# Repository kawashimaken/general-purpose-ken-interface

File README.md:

# KEN Interface

A modular, multi-MCU prototyping platform with a unified pin-assignment standard and horizontally-stackable expansion boards.

> **Status**: Hardware design (KiCad) is published in this repository. Software libraries (Hardware Abstraction Layer and demo applications) are **under active development** and will be released separately in the near future.

---

## 📺 Watch the Introduction

---

## What is KEN Interface?

At its core, **KEN Interface is a standardized pin-assignment pattern shared between MCU boards and expansion boards.**

If you have worked with Arduino shields, the idea will feel familiar — because the pin layout is fixed, any compatible expansion board just plugs straight in and works. KEN Interface follows the same philosophy, but with a few key differences.

### Three Distinctive Features

#### 1. Horizontal Expansion

Instead of stacking boards vertically like Arduino shields, KEN Interface uses **15×2 right-angle pin headers** so boards connect **side by side**. The left and right connectors are completely symmetrical — it does not matter which side you plug into.

Add a **junction board** into the mix, and you can expand in multiple directions: left, right, up, down. Since nothing is buried under another board, every module stays visible, and you can read the pin labels right off the PCB. No more hunting for which wire goes where.

#### 2. Multi-MCU Support

KEN Interface currently supports **four MCUs**:

| MCU | Notes |
|---|---|
| **ESP32** (WROOM-32) | Wi-Fi / BLE built-in |
| **ESP32-S3** (WROOM-1) | Wi-Fi / BLE / native USB / dual core |
| **Raspberry Pi Pico** (RP2040) | Dual core, PIO for I2S, low cost |
| **STM32G431** (WeAct CBU6) | 170 MHz, real DSP, hardware FPU |

The same expansion board works with all of them. **Swap the MCU board, and you are good to go — no rewiring required.**

#### 3. Software Portability

Even though each MCU uses different physical pin numbers, the **functional pin groups sit at fixed positions** across all KEN Interface boards. Build your code around a HAL (Hardware Abstraction Layer), and a single codebase can run on all four MCUs.

> The Ken Interface software library that provides this HAL is currently being developed and will be released in a separate repository.

---

## Pin Assignment Design

The pin layout exposes the default peripheral interfaces that most modern MCUs provide out of the box.

### Functional Pin Groups

| Group | Purpose |
|---|---|
| **UART_A** | General-purpose serial communication |
| **UART_B** | Secondary serial / debugging (some MCUs have native USB instead) |
| **I2C** | Sensors, OLEDs, character LCDs, I/O expanders |
| **SPI** | TFT displays, fast peripherals |
| **I2S_A / I2S_B** | Microphones, digital audio (PIO emulation on Pico) |
| **PWM_A — PWM_F** | DC motors, stepper motors, BLDC motors, servos |
| **ADC_A / ADC_B** | Analog inputs (sensors, joysticks) |
| **Power rails** | 3.3 V and 5 V |

### Design Principle

> *"If the MCU supports it, we connect it. If it does not, it is just **Not Available**."*

Not every MCU covers every group. For example:
- ESP32 (WROOM-32) does not expose UART_B (limited free GPIO).
- STM32G431 shares some SPI and PWM pins due to peripheral multiplexing constraints.

These were deliberate trade-offs, figured out the hard way through multiple board revisions.

### Detailed Pin Mapping

The complete pin assignment matrix across all four MCUs is documented in the KiCad schematic and accompanying spreadsheet (see [`kicad/`](./kicad/)).

---

## What Is in This Repository

```
.
├── kicad/              KiCad PCB project — schematic, board, and gerbers
├── LICENSE             MIT License
└── README.md           This file
```

Currently this repository contains the **hardware design only** (KiCad project for the KEN Interface base board and expansion modules).

The accompanying software (HAL library and example applications) is under active development and will be linked here once published.

---

## Hardware

### Connector Specification

- **Side connectors**: 15×2 right-angle pin headers, 2.54 mm pitch
- **Symmetric pinout**: left and right sides are mirror images, so any expansion board can attach to either side
- **Power**: 3.3 V and 5 V rails routed through every connector

### Expansion Boards (existing designs)

Several expansion modules built on KEN Interface:

- **SPI TFT display board** (ILI9341, 2.4-inch)
- **I2S microphone + audio amplifier board**
- **MCP23008 I/O expander + analog joystick board**
- **BLDC motor driver board** (3-PWM, for SmartKnob / SimpleFOC)
- **Junction board** (4-direction expansion)

---

## Challenges and Limitations

KEN Interface is not a silver bullet. A few honest caveats:

- **Manufacturing cost.** Symmetric routing tends to push designs toward 4-layer PCBs, making mistakes expensive.
- **Board footprint.** Horizontal expansion uses desk space. KEN Interface is designed for **prototyping and experimentation**, not for final compact products. Once a design is validated, the natural next step is to consolidate everything onto a single custom PCB.
- **Software portability has limits.** A few examples:
  - LovyanGFX does not support STM32G4.
  - STM32G431 often requires SoftWire instead of hardware I2C in this pin layout.
  - Dual-core parallelism is specific to ESP32 / ESP32-S3.
  - I2S microphone support on STM32G431 lacks a ready-made Arduino library.

A well-designed HAL can hide many of these differences, but it cannot eliminate them entirely. KEN Interface provides a common hardware standard and a foundation for HAL design — it does not remove the underlying differences between MCUs.

- **Not for every use case.** Highly specialized projects (large multi-display setups, tightly integrated mechanical builds) may still need fully custom PCBs.

---

## Roadmap

Planned additions include:

- LoRa expansion board
- CAN bus expansion board
- Ethernet expansion board
- Additional sensor modules
- Support for more MCUs
- Dedicated power supply board
- Software HAL library and reference applications (separate repository, coming soon)

---

## Build Your Own

The KiCad project template is published in this repository. If you would like to build your own KEN Interface-compatible board, the schematic symbols, footprints, and design rules are all in [`kicad/`](./kicad/).

Pull requests, design suggestions, and new expansion-board ideas are very welcome.

---

## License

The hardware design files in this repository are released under the **MIT License** (see [LICENSE](./LICENSE)).

Future software components will be released under their own licenses — typically MIT or LGPL — and will be linked from this README once published.

---

## Author

Designed and maintained by **Kawashima Ken** ([@kawashimaken](https://github.com/kawashimaken)).

If you build something with KEN Interface, please consider sharing it — issues, pull requests, and ideas are all welcome.

---

## Acknowledgments

- KEN Interface stands on the shoulders of the wider open-source hardware community: KiCad, Arduino, ESP-IDF, Earle Philhower's Arduino-Pico core, Arduino_Core_STM32, and many display / sensor library authors whose work makes prototyping like this possible.

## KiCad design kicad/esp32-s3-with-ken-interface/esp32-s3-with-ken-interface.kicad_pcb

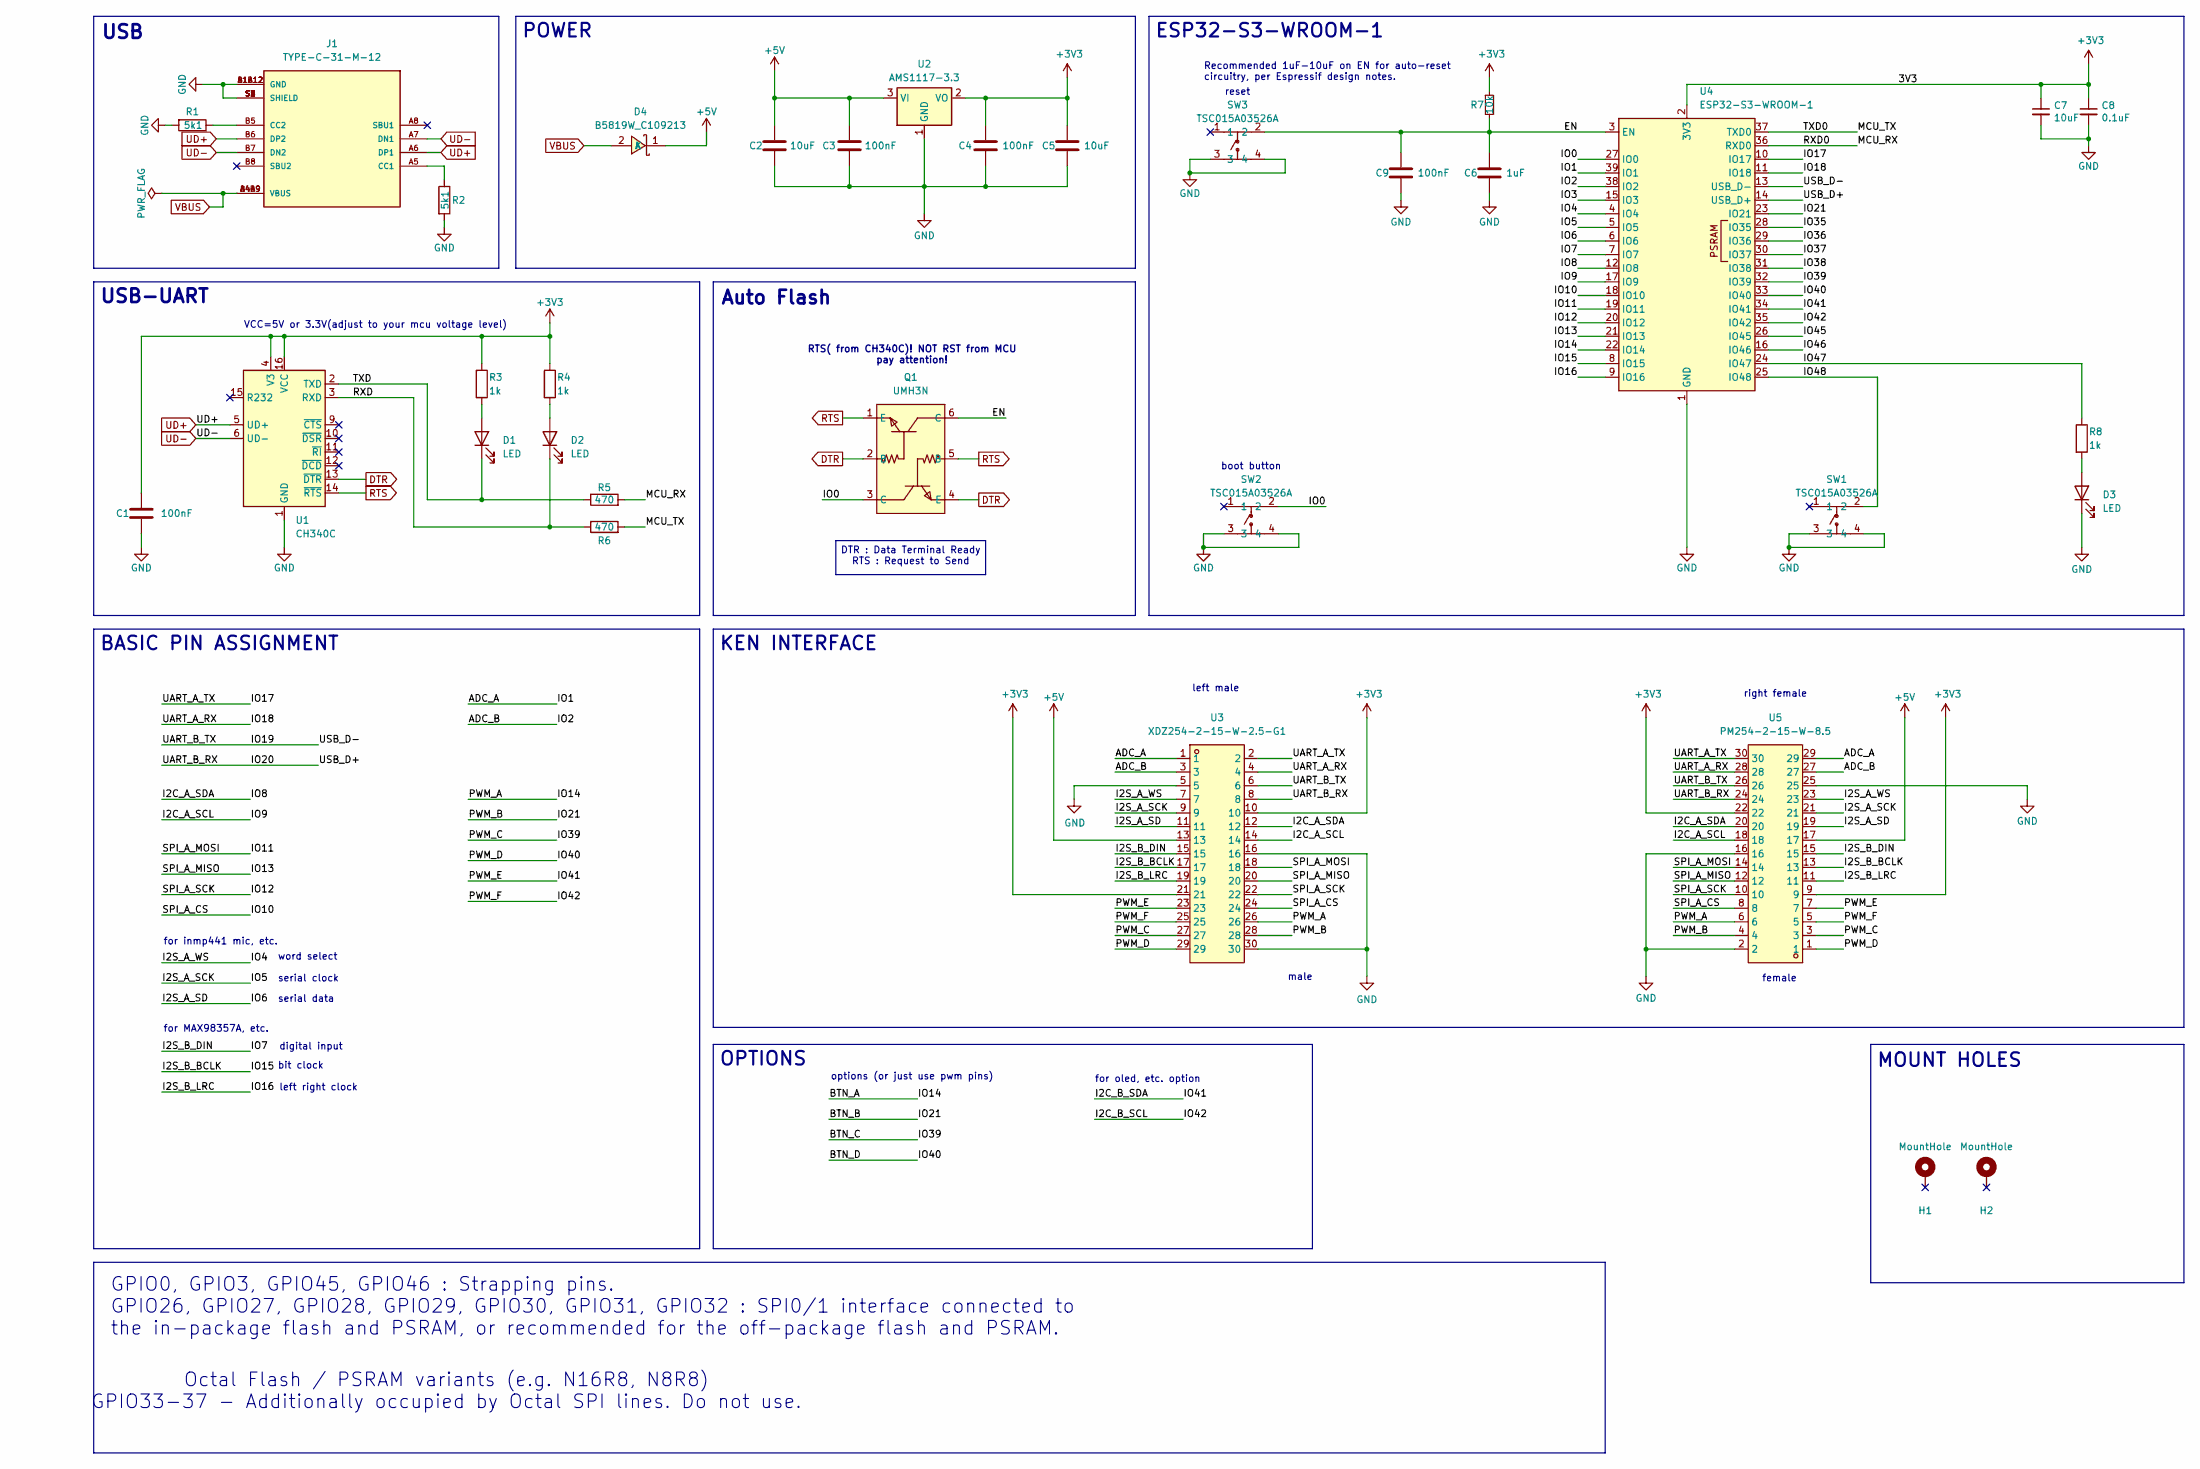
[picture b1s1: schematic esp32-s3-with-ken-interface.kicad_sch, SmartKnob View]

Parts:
C1, C3, C4, C9: 100nF; C_0603_1608Metric_Pad1.08x0.95mm_HandSolder
C2, C5: 10uF; C_1206_3216Metric_Pad1.33x1.80mm_HandSolder
C6: 1uF; C_0603_1608Metric_Pad1.08x0.95mm_HandSolder
C7: 10uF; C_0805_2012Metric_Pad1.18x1.45mm_HandSolder; LCSC C15850
C8: 0.1uF; C_0603_1608Metric_Pad1.08x0.95mm_HandSolder; LCSC C1591
D1, D2, D3: LED; LED_1206_3216Metric_Pad1.42x1.75mm_HandSolder
D4: B5819W_C109213; SOD-123_L2.8-W1.8-LS3.7-RD; LCSC Part C109213
H1, H2: MountHole; MountingHole_3.2mm_M3_DIN965_Pad; LCSC C2911210 or C2911532 (screw), C2961595 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
J1: TYPE-C-31-M-12; HRO_TYPE-C-31-M-12; PARTREV A
Q1: UMH3N; SC-70-6_L2.2-W1.3-P0.65-LS2.1-BR; LCSC Part C62892
R1, R2: 5k1; R_0603_1608Metric_Pad0.98x0.95mm_HandSolder
R3, R4, R8: 1k; R_0603_1608Metric_Pad0.98x0.95mm_HandSolder
R5, R6: 470; R_0603_1608Metric_Pad0.98x0.95mm_HandSolder
R7: 10k; R_0603_1608Metric_Pad0.98x0.95mm_HandSolder; LCSC C98220
SW1, SW2, SW3: TSC015A03526A; SW-SMD_4P-L4.5-W4.5-P3.00-LS6.8; LCSC Part C2888900
U1: CH340C; SOIC-16_3.9x9.9mm_P1.27mm
U2: AMS1117-3.3; SOT-223-3_TabPin2
U3: XDZ254-2-15-W-2.5-G1; HDR-TH_30P-P2.54-H-M-R2-C15-S2.54-N; LCSC Part C18905913
U4: ESP32-S3-WROOM-1
U5: PM254-2-15-W-8.5; HDR-TH_30P-P2.54-H-F-R2-C15-W8.5; LCSC Part C2897435

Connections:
+3V3: C1.1, C4.1, C5.1, C7.1, C8.1, R3.1, R4.1, R7.1, U1.4 (V3), U1.16 (VCC), U2.2 (VO), U3.10, U3.21, U4.2 (3V3), U5.9, U5.22
+5V: C2.1, C3.1, D4.1 (K), U2.3 (VI), U3.13, U5.17
/ADC_A: U3.1, U4.39 (IO1), U5.29
/ADC_B: U3.3, U4.38 (IO2), U5.27
/BTN_A: U3.26, U4.22 (IO14), U5.6
/BTN_B: U3.28, U4.23 (IO21), U5.4
/BTN_C: U3.27, U4.32 (IO39), U5.3
/BTN_D: U3.29, U4.33 (IO40), U5.1
/EN: C6.1, C9.1, Q1.6 (C), R7.2, SW3.2, U4.3 (EN)
/I2C_A_SCL: U3.14, U4.17 (IO9), U5.18
/I2C_A_SDA: U3.12, U4.12 (IO8), U5.20
/I2C_B_SCL: U3.25, U4.35 (IO42), U5.5
/I2C_B_SDA: U3.23, U4.34 (IO41), U5.7
/I2S_A_SCK: U3.9, U4.5 (IO5), U5.21
/I2S_A_SD: U3.11, U4.6 (IO6), U5.19
/I2S_A_WS: U3.7, U4.4 (IO4), U5.23
/I2S_B_BCLK: U3.17, U4.8 (IO15), U5.13
/I2S_B_DIN: U3.15, U4.7 (IO7), U5.15
/I2S_B_LRC: U3.19, U4.9 (IO16), U5.11
/IO0: Q1.3 (C), SW2.2, U4.27 (IO0)
/IO3: U4.15 (IO3)
/IO10: U3.24, U4.18 (IO10), U5.8
/IO11: U3.18, U4.19 (IO11), U5.14
/IO12: U3.22, U4.20 (IO12), U5.10
/IO13: U3.20, U4.21 (IO13), U5.12
/IO17: U3.2, U4.10 (IO17), U5.30
/IO18: U3.4, U4.11 (IO18), U5.28
/IO19: U3.6, U4.13 (USB_D-), U5.26
/IO20: U3.8, U4.14 (USB_D+), U5.24
/IO35: U4.28 (IO35)
/IO36: U4.29 (IO36)
/IO37: U4.30 (IO37)
/IO38: U4.31 (IO38)
/IO45: U4.26 (IO45)
/IO46: U4.16 (IO46)
/IO47: R8.1, U4.24 (IO47)
/IO48: SW1.2, U4.25 (IO48)
/MCU_RX: R5.2, U4.36 (RXD0)
/MCU_TX: R6.2, U4.37 (TXD0)
/RXD: D2.1 (K), R6.1, U1.3 (RXD)
/TXD: D1.1 (K), R5.1, U1.2 (TXD)
DTR: Q1.2 (B), Q1.4 (E), U1.13 (~DTR)
GND: C1.2, C2.2, C3.2, C4.2, C5.2, C6.2, C7.2, C8.2, C9.2, D3.1 (K), J1.A1B12 (GND), J1.B1A12 (GND), J1.S1 (SHIELD), J1.S2 (SHIELD), J1.S3 (SHIELD), J1.S4 (SHIELD), R1.2, R2.2, SW1.3, SW1.4, SW2.3, SW2.4, SW3.3, SW3.4, U1.1 (GND), U2.1 (GND), U3.5, U3.16, U3.30, U4.1 (GND), U4.40 (GND), U4.41 (GND), U5.2, U5.16, U5.25
unnamed: D1.2 (A), R3.2
unnamed: D2.2 (A), R4.2
unnamed: D3.2 (A), R8.2
unnamed: J1.A5 (CC1), R2.1
unnamed: J1.B5 (CC2), R1.1
RTS: Q1.1 (E), Q1.5 (B), U1.14 (~RTS)
UD+: J1.A6 (DP1), J1.B6 (DP2), U1.5 (UD+)
UD-: J1.A7 (DN1), J1.B7 (DN2), U1.6 (UD-)
VBUS: D4.2 (A), J1.A4B9 (VBUS), J1.B4A9 (VBUS)

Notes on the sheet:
POWER
VCC=5V or 3.3V(adjust to your mcu voltage level)
for MAX98357A, etc.
USB
KEN INTERFACE
GPIO0, GPIO3, GPIO45, GPIO46 : Strapping pins. GPIO26, GPIO27, GPIO28, GPIO29, GPIO30, GPIO31, GPIO32 : SPI0/1 interface connected to the in-package flash and PSRAM, or recommended for the off-package flash and PSRAM.
MOUNT HOLES
right female
RTS( from CH340C)! NOT RST from MCU pay attention!
female
word select
BASIC PIN ASSIGNMENT
male
serial clock
left right clock
Octal Flash / PSRAM variants (e.g. N16R8, N8R8) GPIO33-37 - Additionally occupied by Octal SPI lines. Do not use.
bit clock
left male
ESP32-S3-WROOM-1
OPTIONS
Recommended 1uF-10uF on EN for auto-reset circuitry, per Espressif design notes.
USB-UART
boot button
reset
options (or just use pwm pins)
digital input
serial data
for oled, etc. option
for inmp441 mic, etc.
Auto Flash
DTR : Data Terminal Ready RTS : Request to Send

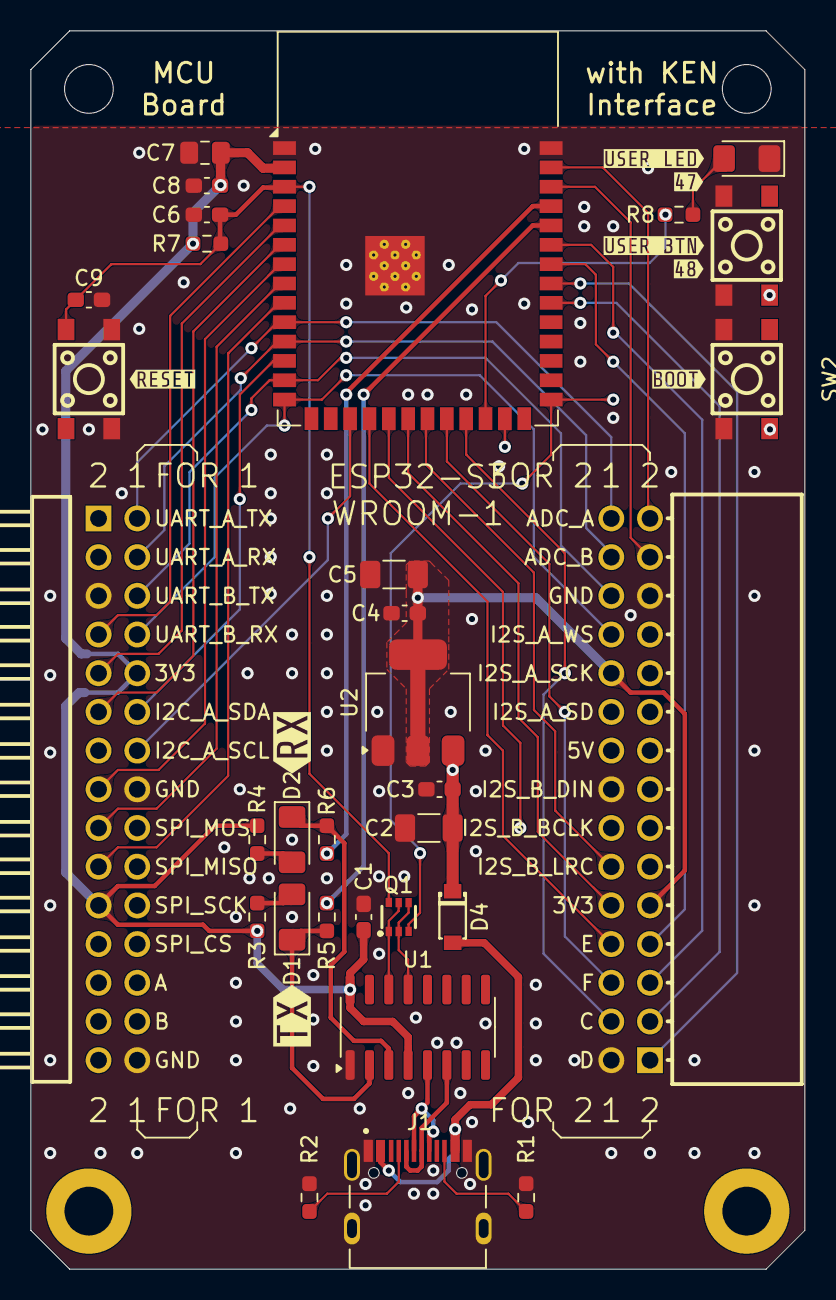
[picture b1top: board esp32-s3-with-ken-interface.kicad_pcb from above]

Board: 4 copper layers, 50.8 x 81.3 mm, 41 parts (0 on the bottom side), 45 nets.

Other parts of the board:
kibuzzard-69BBE7EF: G***; kibuzzard-69BBE7EF
kibuzzard-69BBE90D: G***; kibuzzard-69BBE90D
kibuzzard-69BBF8B2: G***; kibuzzard-69BBF8B2
kibuzzard-69BBF8C4: G***; kibuzzard-69BBF8C4
kibuzzard-69BBF8DF: G***; kibuzzard-69BBF8DF
kibuzzard-696F5E7C: G***; kibuzzard-696F5E7C
kibuzzard-696F5E93: G***; kibuzzard-696F5E93
kibuzzard-69756FE8: G***; kibuzzard-69756FE8

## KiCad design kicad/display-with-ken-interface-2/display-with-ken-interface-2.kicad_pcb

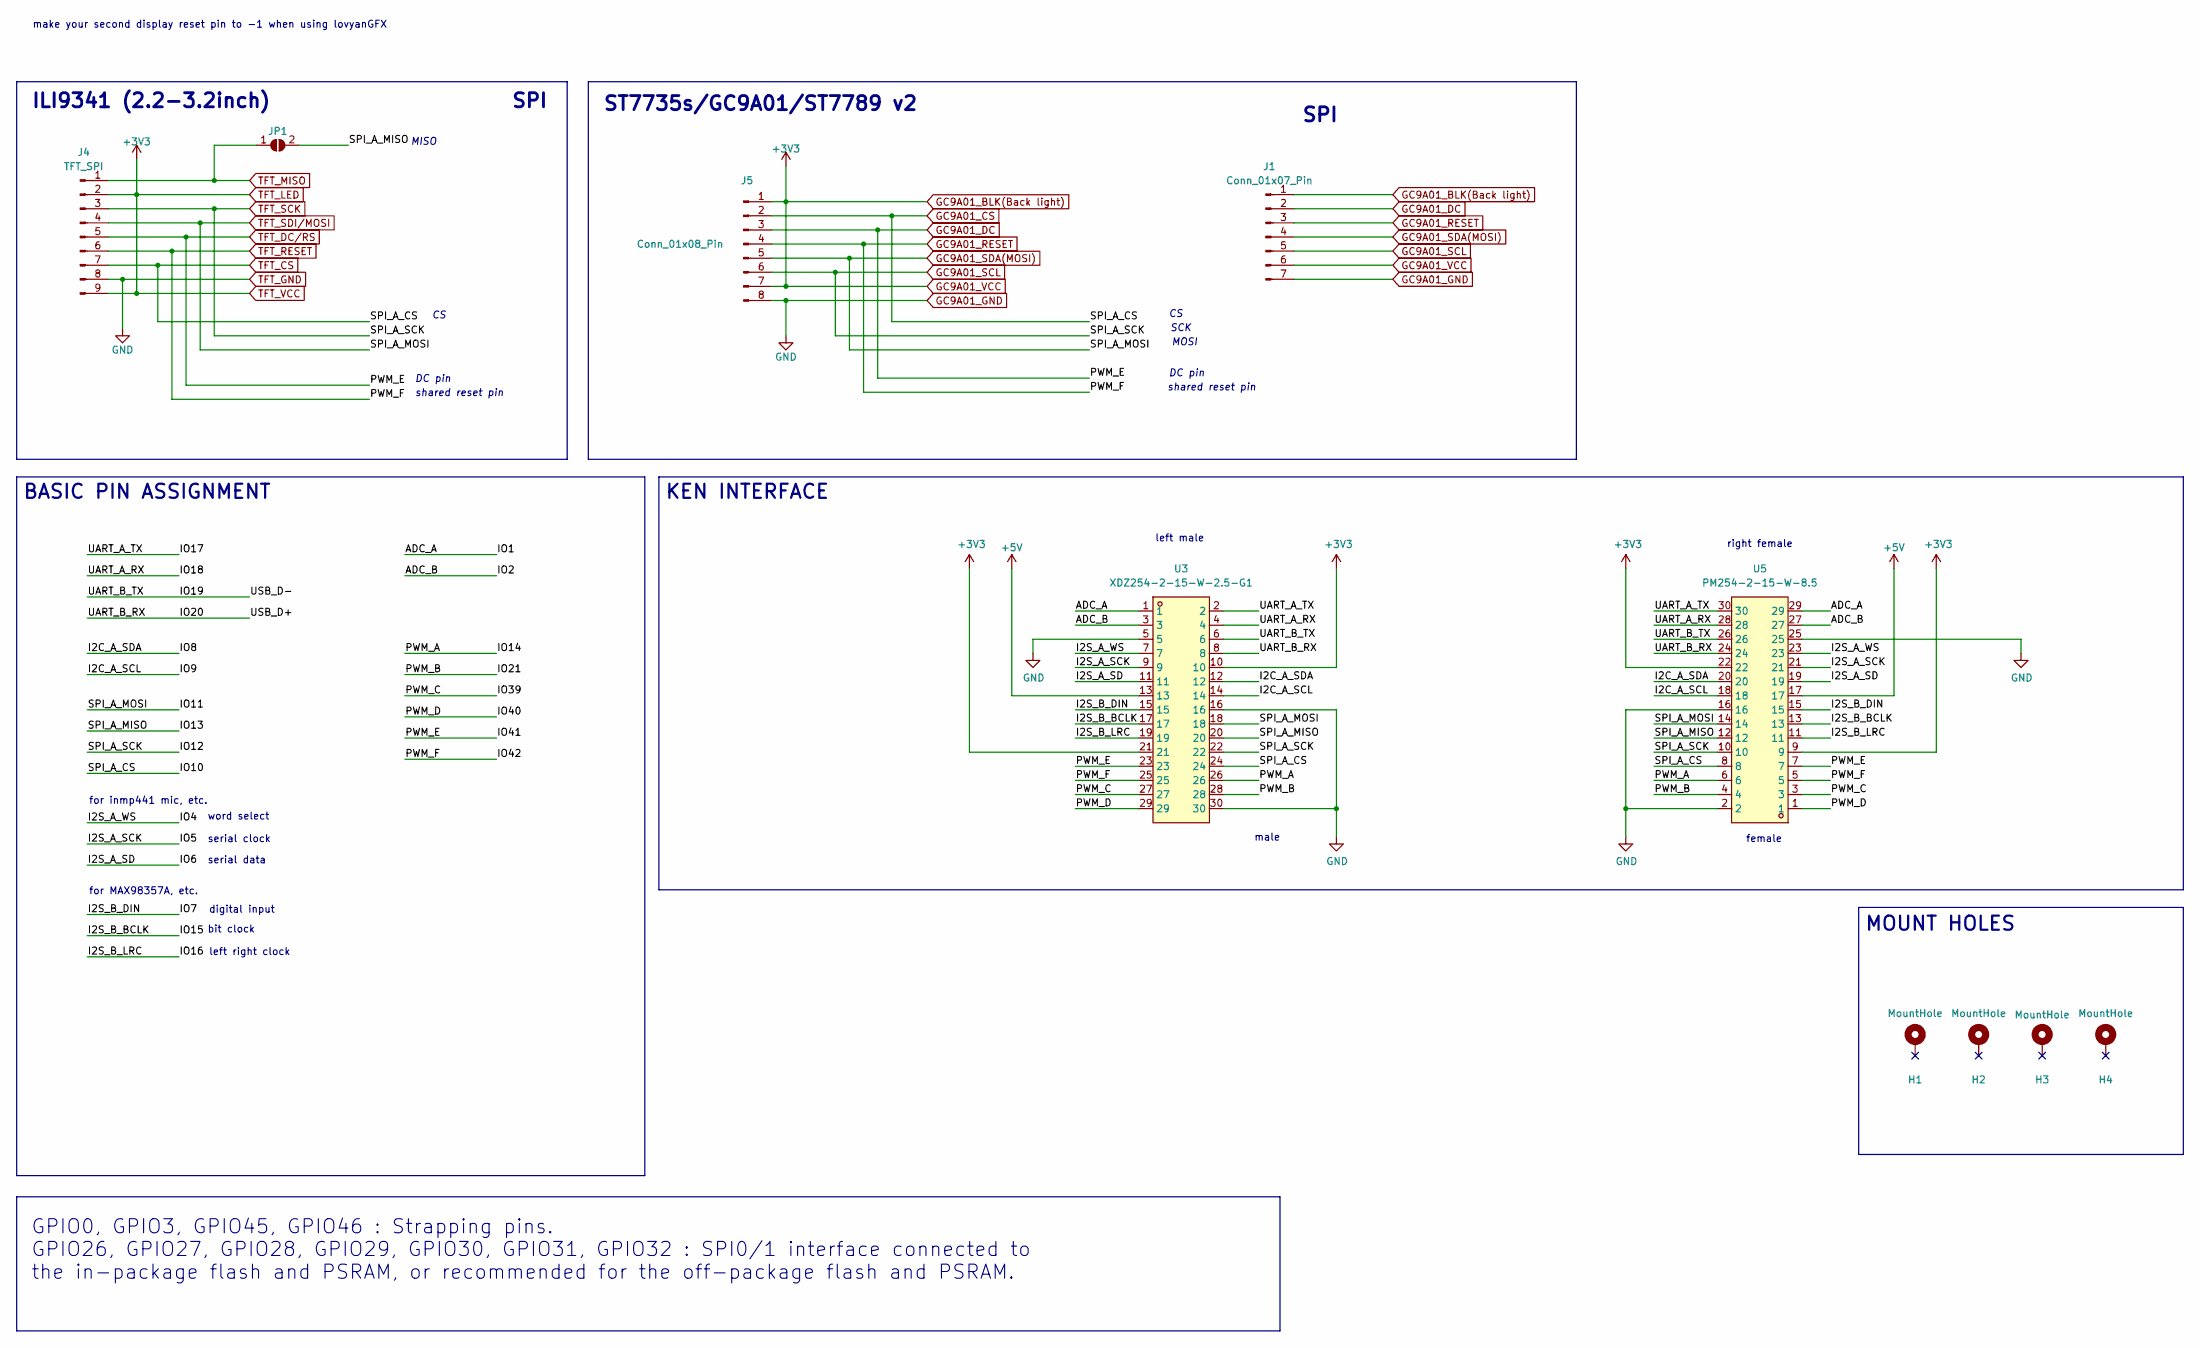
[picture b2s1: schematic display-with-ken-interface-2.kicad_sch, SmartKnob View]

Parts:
H1, H2, H3, H4: MountHole; MountingHole_3.2mm_M3_DIN965_Pad; LCSC C2911210 or C2911532 (screw), C2961595 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
J1: Conn_01x07_Pin; PinHeader_1x07_P2.54mm_Vertical
J4: TFT_SPI; PinHeader_1x09_P2.54mm_Vertical
J5: Conn_01x08_Pin; PinHeader_1x08_P2.54mm_Vertical
JP1: SolderJumper_2_Open; SolderJumper-2_P1.3mm_Open_RoundedPad1.0x1.5mm
U3: XDZ254-2-15-W-2.5-G1; HDR-TH_30P-P2.54-H-M-R2-C15-S2.54-N; LCSC Part C18905913
U5: PM254-2-15-W-8.5; HDR-TH_30P-P2.54-H-F-R2-C15-W8.5; LCSC Part C2897435

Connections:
+5V: U3.13, U5.17
/ADC_A: U3.1, U5.29
/ADC_B: U3.3, U5.27
/I2C_A_SCL: U3.14, U5.18
/I2C_A_SDA: U3.12, U5.20
/I2S_A_SCK: U3.9, U5.21
/I2S_A_SD: U3.11, U5.19
/I2S_A_WS: U3.7, U5.23
/I2S_B_BCLK: U3.17, U5.13
/I2S_B_DIN: U3.15, U5.15
/I2S_B_LRC: U3.19, U5.11
/IO13: JP1.2 (B), U3.20, U5.12
/IO14: U3.26, U5.6
/IO17: U3.2, U5.30
/IO18: U3.4, U5.28
/IO19: U3.6, U5.26
/IO20: U3.8, U5.24
/IO21: U3.28, U5.4
/IO39: U3.27, U5.3
/IO40: U3.29, U5.1
GC9A01_BLK(Back light): J1.1, J1.6, J4.2, J4.9, J5.1, J5.7, U3.10, U3.21, U5.9, U5.22
GC9A01_CS: J4.7, J5.2, U3.24, U5.8
GC9A01_DC: J1.2, J4.5, J5.3, U3.23, U5.7
GC9A01_GND: J1.7, J4.8, J5.8, U3.5, U3.16, U3.30, U5.2, U5.16, U5.25
GC9A01_RESET: J1.3, J4.6, J5.4, U3.25, U5.5
GC9A01_SCL: J1.5, J4.3, J5.6, U3.22, U5.10
GC9A01_SDA(MOSI): J1.4, J4.4, J5.5, U3.18, U5.14
TFT_MISO: J4.1, JP1.1 (A)

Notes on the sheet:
shared reset pin
for MAX98357A, etc.
KEN INTERFACE
GPIO0, GPIO3, GPIO45, GPIO46 : Strapping pins. GPIO26, GPIO27, GPIO28, GPIO29, GPIO30, GPIO31, GPIO32 : SPI0/1 interface connected to the in-package flash and PSRAM, or recommended for the off-package flash and PSRAM.
SCK
SPI
MOUNT HOLES
right female
female
DC pin
word select
MISO
BASIC PIN ASSIGNMENT
male
serial clock
left right clock
bit clock
MOSI
left male
ST7735s/GC9A01/ST7789 v2
ILI9341 (2.2-3.2inch)
digital input
serial data
make your second display reset pin to -1 when using lovyanGFX
for inmp441 mic, etc.

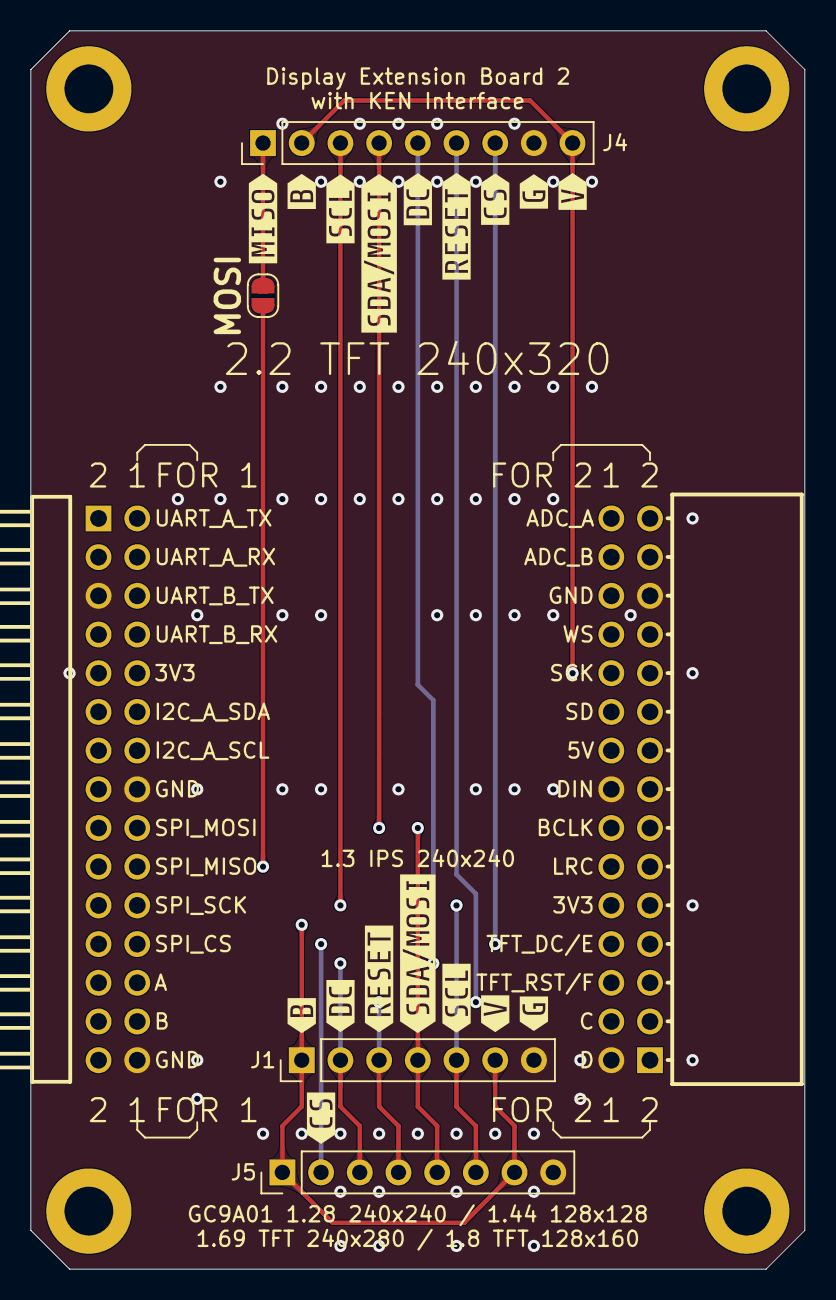
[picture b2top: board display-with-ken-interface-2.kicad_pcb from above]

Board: 4 copper layers, 50.8 x 81.3 mm, 27 parts (0 on the bottom side), 28 nets.

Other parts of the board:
kibuzzard-69E872B6: G***; kibuzzard-69E872B6
kibuzzard-69E872D5: G***; kibuzzard-69E872D5
kibuzzard-69E874A0: G***; kibuzzard-69E874A0
kibuzzard-69E874A4: G***; kibuzzard-69E874A4
kibuzzard-69E874AD: G***; kibuzzard-69E874AD
kibuzzard-69E874B2: G***; kibuzzard-69E874B2
kibuzzard-69E8720F: G***; kibuzzard-69E8720F
kibuzzard-69E8724B: G***; kibuzzard-69E8724B
kibuzzard-69E8725D: G***; kibuzzard-69E8725D
kibuzzard-69E8747C: G***; kibuzzard-69E8747C
kibuzzard-69E8749A: G***; kibuzzard-69E8749A
kibuzzard-69E87221: G***; kibuzzard-69E87221
kibuzzard-69E87232: G***; kibuzzard-69E87232
kibuzzard-69E87269: G***; kibuzzard-69E87269
kibuzzard-69E87476: G***; kibuzzard-69E87476
kibuzzard-69E87482: G***; kibuzzard-69E87482
kibuzzard-69E87487: G***; kibuzzard-69E87487

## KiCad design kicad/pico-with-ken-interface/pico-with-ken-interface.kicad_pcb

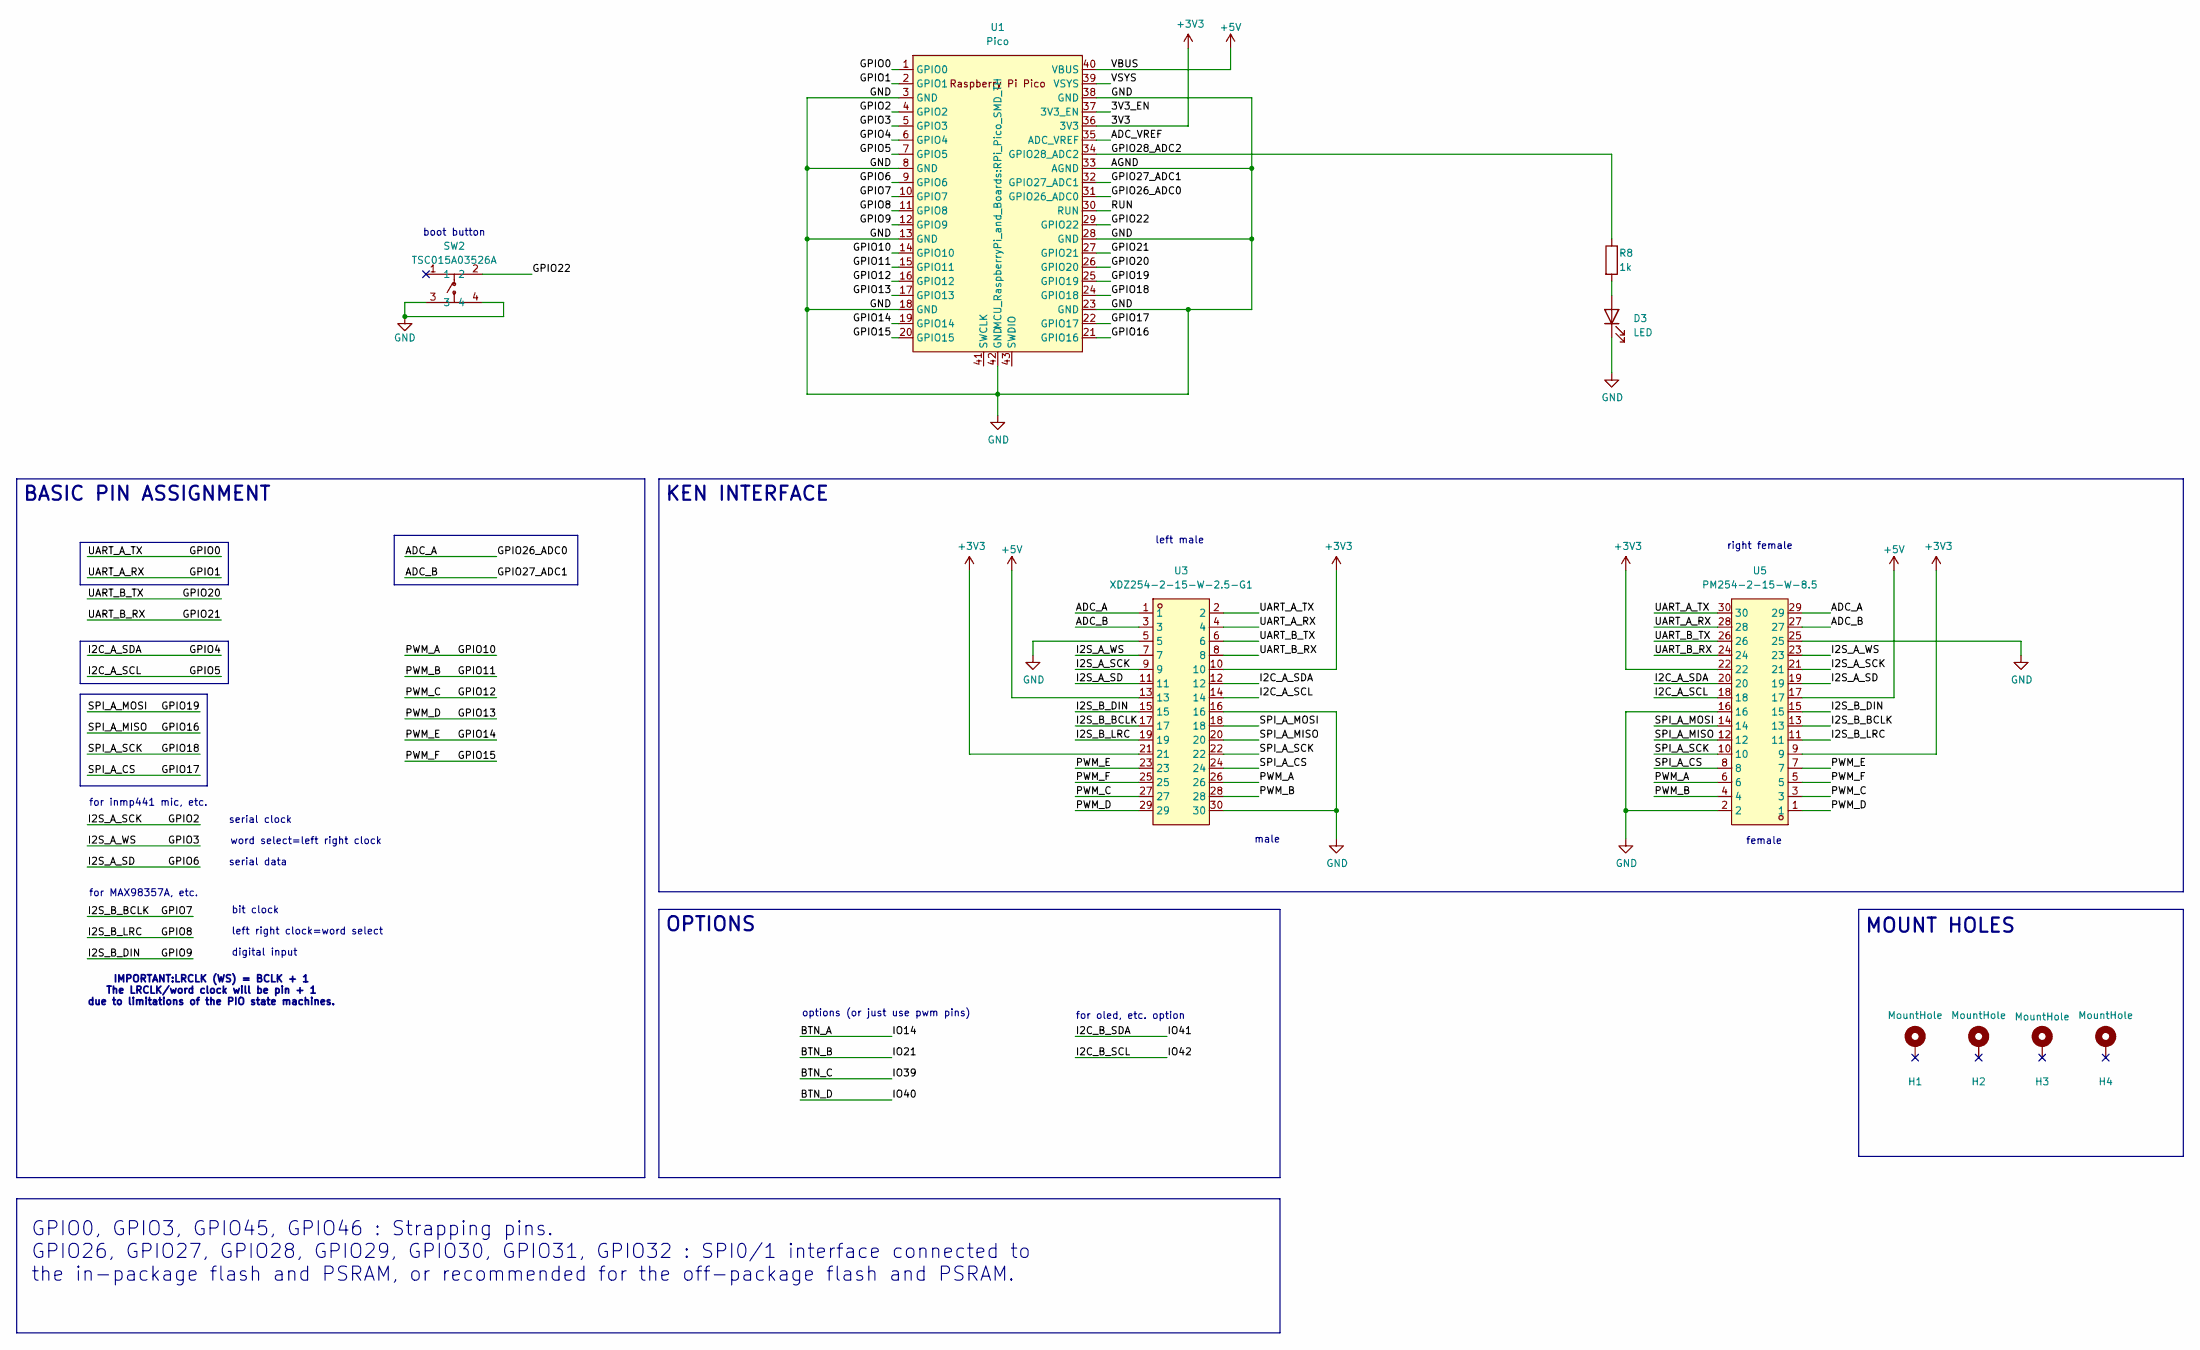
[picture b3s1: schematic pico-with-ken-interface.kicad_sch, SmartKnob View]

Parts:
D3: LED; LED_1206_3216Metric_Pad1.42x1.75mm_HandSolder
H1, H2, H3, H4: MountHole; MountingHole_3.2mm_M3_DIN965_Pad; LCSC C2911210 or C2911532 (screw), C2961595 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
R8: 1k; R_0603_1608Metric_Pad0.98x0.95mm_HandSolder
SW2: TSC015A03526A; SW-SMD_4P-L4.5-W4.5-P3.00-LS6.8; LCSC Part C2888900
U1: Pico; RPi_Pico_SMD_TH
U3: XDZ254-2-15-W-2.5-G1; HDR-TH_30P-P2.54-H-M-R2-C15-S2.54-N; LCSC Part C18905913
U5: PM254-2-15-W-8.5; HDR-TH_30P-P2.54-H-F-R2-C15-W8.5; LCSC Part C2897435

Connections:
+3V3: U1.36 (3V3), U3.10, U3.21, U5.9, U5.22
+5V: U1.40 (VBUS), U3.13, U5.17
/3V3_EN: U1.37 (3V3_EN)
/ADC_A: U1.31 (GPIO26_ADC0), U3.1, U5.29
/ADC_B: U1.32 (GPIO27_ADC1), U3.3, U5.27
/ADC_VREF: U1.35 (ADC_VREF)
/GPIO0: U1.1 (GPIO0), U3.2, U5.30
/GPIO1: U1.2 (GPIO1), U3.4, U5.28
/GPIO2: U1.4 (GPIO2), U3.9, U5.21
/GPIO3: U1.5 (GPIO3), U3.7, U5.23
/GPIO4: U1.6 (GPIO4), U3.12, U5.20
/GPIO5: U1.7 (GPIO5), U3.14, U5.18
/GPIO6: U1.9 (GPIO6), U3.11, U5.19
/GPIO7: U1.10 (GPIO7), U3.17, U5.13
/GPIO8: U1.11 (GPIO8), U3.19, U5.11
/GPIO9: U1.12 (GPIO9), U3.15, U5.15
/GPIO10: U1.14 (GPIO10), U3.26, U5.6
/GPIO11: U1.15 (GPIO11), U3.28, U5.4
/GPIO12: U1.16 (GPIO12), U3.27, U5.3
/GPIO13: U1.17 (GPIO13), U3.29, U5.1
/GPIO14: U1.19 (GPIO14), U3.23, U5.7
/GPIO15: U1.20 (GPIO15), U3.25, U5.5
/GPIO16: U1.21 (GPIO16), U3.20, U5.12
/GPIO17: U1.22 (GPIO17), U3.24, U5.8
/GPIO18: U1.24 (GPIO18), U3.22, U5.10
/GPIO19: U1.25 (GPIO19), U3.18, U5.14
/GPIO20: U1.26 (GPIO20), U3.6, U5.26
/GPIO21: U1.27 (GPIO21), U3.8, U5.24
/GPIO22: SW2.2, U1.29 (GPIO22)
/GPIO28_ADC2: R8.1, U1.34 (GPIO28_ADC2)
/RUN: U1.30 (RUN)
/VSYS: U1.39 (VSYS)
GND: D3.1 (K), SW2.3, SW2.4, U1.3 (GND), U1.8 (GND), U1.13 (GND), U1.18 (GND), U1.23 (GND), U1.28 (GND), U1.33 (AGND), U1.38 (GND), U1.42 (GND), U3.5, U3.16, U3.30, U5.2, U5.16, U5.25
unnamed: D3.2 (A), R8.2

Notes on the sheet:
IMPORTANT:LRCLK (WS) = BCLK + 1 The LRCLK/word clock will be pin + 1 due to limitations of the PIO state machines.
for MAX98357A, etc.
KEN INTERFACE
GPIO0, GPIO3, GPIO45, GPIO46 : Strapping pins. GPIO26, GPIO27, GPIO28, GPIO29, GPIO30, GPIO31, GPIO32 : SPI0/1 interface connected to the in-package flash and PSRAM, or recommended for the off-package flash and PSRAM.
MOUNT HOLES
right female
female
word select=left right clock
BASIC PIN ASSIGNMENT
male
serial clock
left right clock=word select
bit clock
left male
OPTIONS
options (or just use pwm pins)
digital input
serial data
for oled, etc. option
for inmp441 mic, etc.
boot button

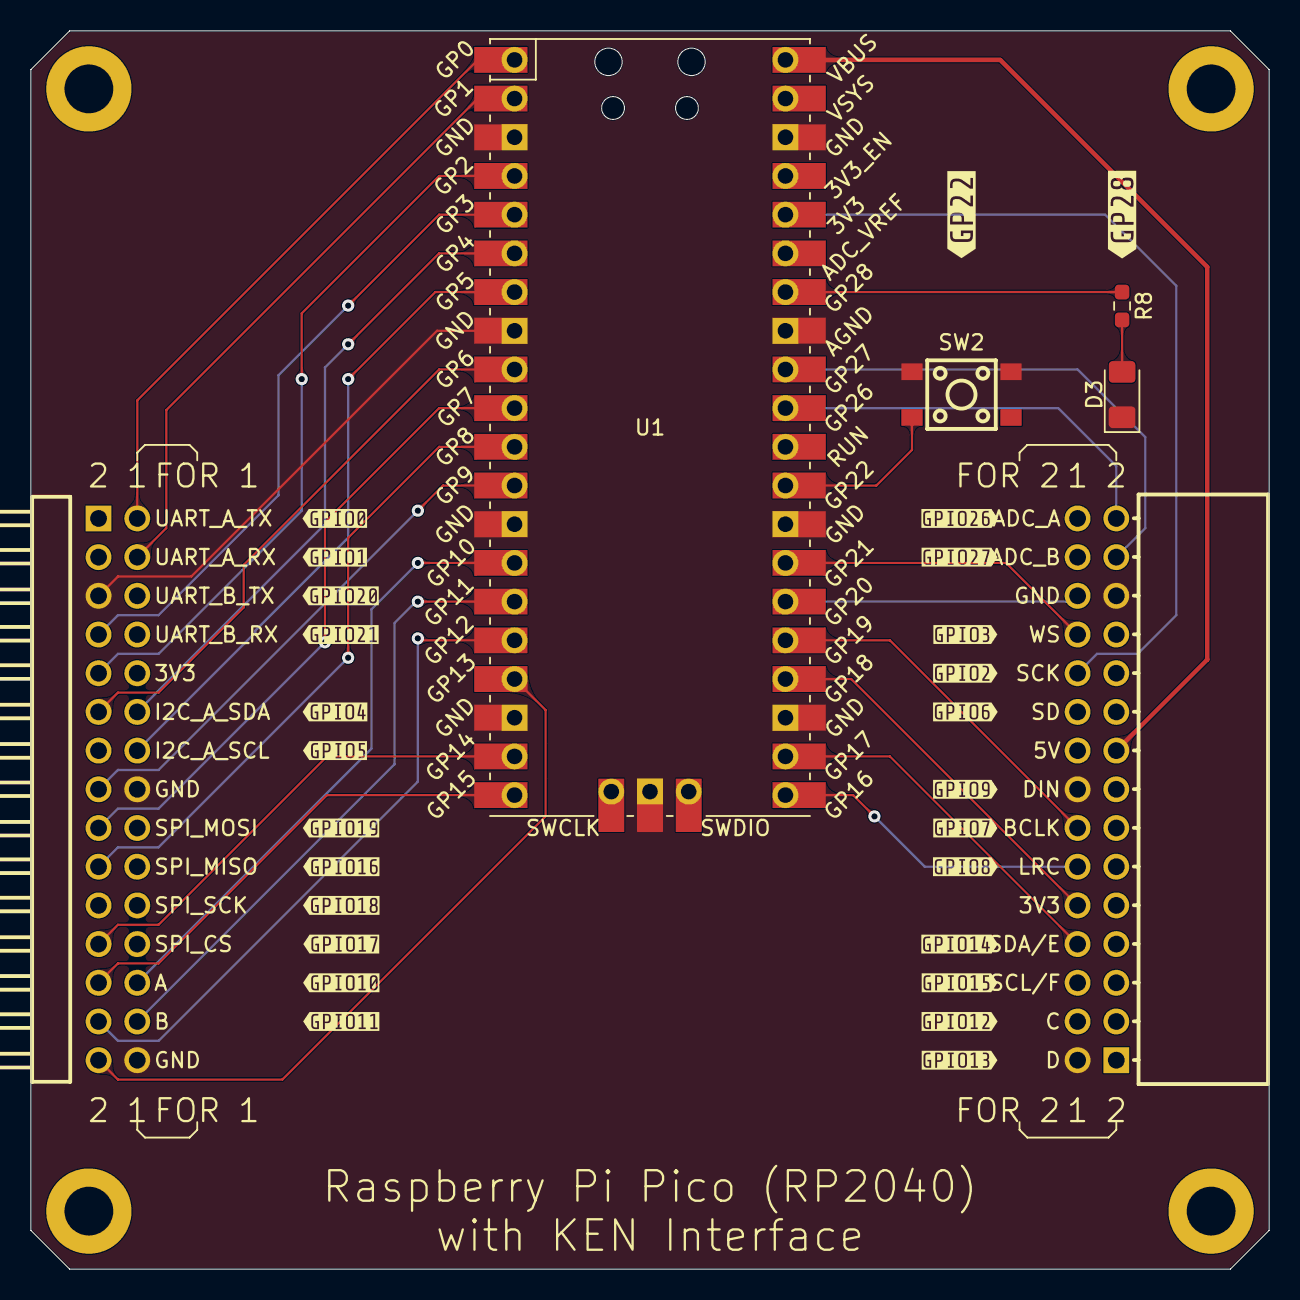
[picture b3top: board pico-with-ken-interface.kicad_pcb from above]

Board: 4 copper layers, 81.3 x 81.3 mm, 36 parts (0 on the bottom side), 30 nets.

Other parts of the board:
kibuzzard-69ABCB94: G***; kibuzzard-69ABCB94
kibuzzard-69ABCBB2: G***; kibuzzard-69ABCBB2
kibuzzard-69B2BBD5: G***; kibuzzard-69B2BBD5
kibuzzard-69B2BBE8: G***; kibuzzard-69B2BBE8
kibuzzard-69B2BC4D: G***; kibuzzard-69B2BC4D
kibuzzard-69B2BC5B: G***; kibuzzard-69B2BC5B
kibuzzard-69B2BC8C: G***; kibuzzard-69B2BC8C
kibuzzard-69B2BC9C: G***; kibuzzard-69B2BC9C
kibuzzard-69B2BC53: G***; kibuzzard-69B2BC53
kibuzzard-69B2BC62: G***; kibuzzard-69B2BC62
kibuzzard-69B2BC71: G***; kibuzzard-69B2BC71
kibuzzard-69B2BCA8: G***; kibuzzard-69B2BCA8
kibuzzard-69B2BCB2: G***; kibuzzard-69B2BCB2
kibuzzard-69B2BCDF: G***; kibuzzard-69B2BCDF
kibuzzard-69B2BD0A: G***; kibuzzard-69B2BD0A
kibuzzard-69B2BD8D: G***; kibuzzard-69B2BD8D
kibuzzard-69B2BD9D: G***; kibuzzard-69B2BD9D
kibuzzard-69B2BD17: G***; kibuzzard-69B2BD17
kibuzzard-69B2BD42: G***; kibuzzard-69B2BD42
kibuzzard-69B2BD56: G***; kibuzzard-69B2BD56
kibuzzard-69B2BD62: G***; kibuzzard-69B2BD62
kibuzzard-69B2BD76: G***; kibuzzard-69B2BD76
kibuzzard-69B2BD80: G***; kibuzzard-69B2BD80
kibuzzard-69B2BDB2: G***; kibuzzard-69B2BDB2
kibuzzard-69B2BDBA: G***; kibuzzard-69B2BDBA
kibuzzard-69B2BDC4: G***; kibuzzard-69B2BDC4
